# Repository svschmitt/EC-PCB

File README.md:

# EC-PCB
Arduino interface for communication with the Entertainment &amp; Comfort serial bus found in some GM vehicles.

The EAGLE subdirectory contains EAGLE CAD files for an interface to be used with an Arduino Pro Mini.

The ECcomm_adapter subdirectory contains the sketch to upload to the Arduino. This code could be used with other Arduino variants.

The ECcomm_adapter Arduino sketch can communicate with a serial terminal application as well as the co-developed ECcomm program for Linux (https://github.com/svschmitt/ECcomm/ ), which provides additional functionality included message decoding and bidirectional communication.

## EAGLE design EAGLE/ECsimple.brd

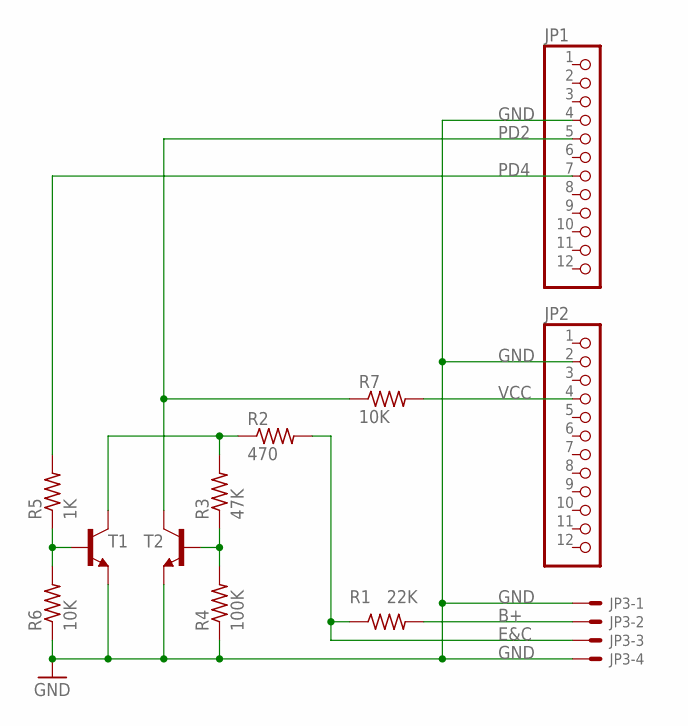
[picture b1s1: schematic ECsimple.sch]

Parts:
JP1, JP2: PINHD-1X12-CB; 1X12-CB
JP3: HDR_PLAIN_1X4; HDR_1X4
R1: 22K; 0204/7
R2: 470; 0204/7
R3: 47K; 0204/7
R4: 100K; 0204/7
R5: 1K; 0204/7
R6, R7: 10K; 0204/7
T1, T2: NPN-TRANSISTORCLEAN; TO92-NONPOLARIZED-CLEAN

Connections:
B+: JP3.2, R1.2
E&C: JP3.3, R1.1, R2.2
GND: JP1.4, JP2.2, JP3.1, JP3.4, R4.1, R6.1, T1.E, T2.E
unnamed: R2.1, R3.2, T1.C
unnamed: R3.1, R4.2, T2.B
unnamed: R5.1, R6.2, T1.B
PD2: JP1.5, R7.1, T2.C
PD4: JP1.7, R5.2
VCC: JP2.4, R7.2

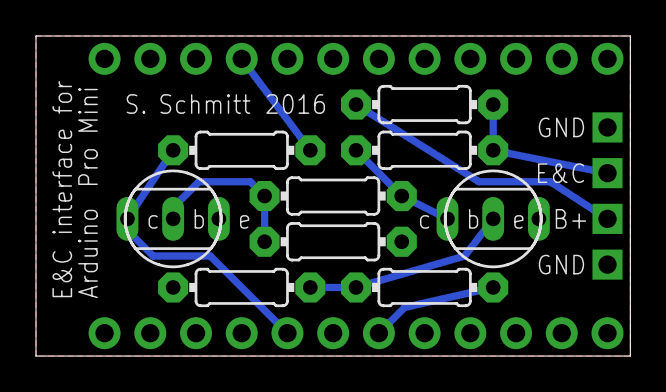
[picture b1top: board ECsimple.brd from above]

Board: 2 copper layers, 33.0 x 17.8 mm, 12 parts (0 on the bottom side), 9 nets.

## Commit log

2016-03-31 Create gh-pages branch via GitHub
2016-05-01 GPL license
2016-05-01 Create COPYING
2016-05-01 Added files via upload
